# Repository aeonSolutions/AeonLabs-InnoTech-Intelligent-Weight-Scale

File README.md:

[PCB-Prototyping-Catalogue](https://github.com/aeonSolutions/PCB-Prototyping-Catalogue)  >>  [Home-Automation](https://github.com/aeonSolutions/PCB-Prototyping-Catalogue/tree/main/Home-Automation)  >>  [Smart Home Appliances](https://github.com/aeonSolutions/PCB-Prototyping-Catalogue/tree/main/Home-Automation/Smart%20Home%20Appliances)  >>  [Bathroom](https://github.com/aeonSolutions/PCB-Prototyping-Catalogue/tree/main/Home-Automation/Smart%20Home%20Appliances/bathroom) >>  InnoTech Intelligent Weight Scale

<br>

<br />

# AeonLabs InnoTech Intelligent Weight Scale
This smart PCB is a direct replacement of the one that is installed on all InnoTech Weight Scales. Features a color LCD and you can connect to your home automation without the need for third-party cloud storage. **This way your health data never leaves your home**.

A breif view of the original specifications:

- Innotech Smart scale analyze 9 essential measurements of your body, including weight, body fat, water, muscle mass, BMI, BMR, visceral fat, bone mass, and protein. Data easily transferred to the Innotech Scale APP as well as other partners' APPs, it will keep you informed about your body data
- Innotech BMI scale can track the measurement for up to 10 users. Innotech Body Fat Scale helps to track and obtain your family’s daily measurements. This Smart Scale is perfect for family, body builder, weight loser
- 4 built-in sensors that ensure accurate measurement up to 397 lbs/180kg in 0.2 lb/0.1kg increments. Our stylish smart scale boosts an extended surface area with resilient tempered glass for durability. The large LED screen easily displays weight without your mobile device

## PCB

## What one additionally needs
- [USB to UART/USB TTL firmware burner for 5V and 3.3V MCUs ](https://github.com/aeonSolutions/PCB-Prototyping-Catalogue/blob/main/DIY-Maker/README.md) 
<br />
<br />

## Author

You can get in touch with me on my LinkedIn Profile:

#### Miguel Tomas

You can also follow my GitHub Profile to stay updated about my latest projects: 

<br>

### Be supportive of my dedication and work towards technology education and buy me a cup of coffee
The PCB Desgin Files i provide here for anyone to use are free. If you like this Smart Device or use it, please consider buying me a cup of coffee, a slice of pizza or a book to help me study, eat and think new PCB design files.

<br />

### Make a donation on Paypal
Make a donation on paypal and get a TAX refund*.

<br>

### Support all these open hardware projects and become a patreon  
Liked any of my PCB KiCad Designs? Help and Support my open work to all by becomming a LDAD Patreon.
In return I will give a free PCB design in KiCad to all patreon supporters. To learn more go to patreon.com. Link below.

<br />
<br />

______________________________________________________________________________________________________________________________
### License
2023 Creative Commons Attribution-NonCommercial-ShareAlike 4.0 International

https://creativecommons.org/licenses/by-nc-sa/4.0/

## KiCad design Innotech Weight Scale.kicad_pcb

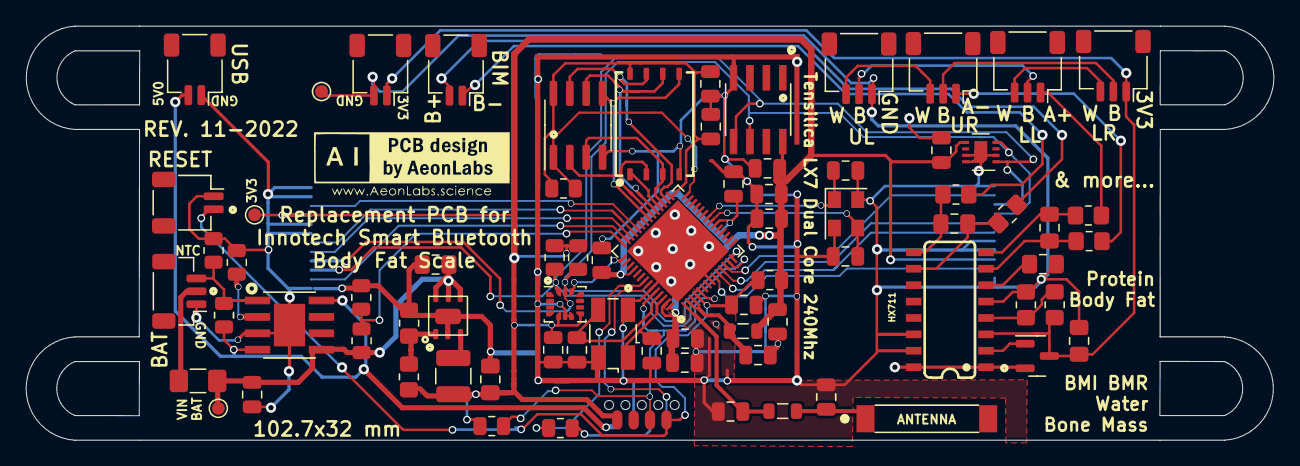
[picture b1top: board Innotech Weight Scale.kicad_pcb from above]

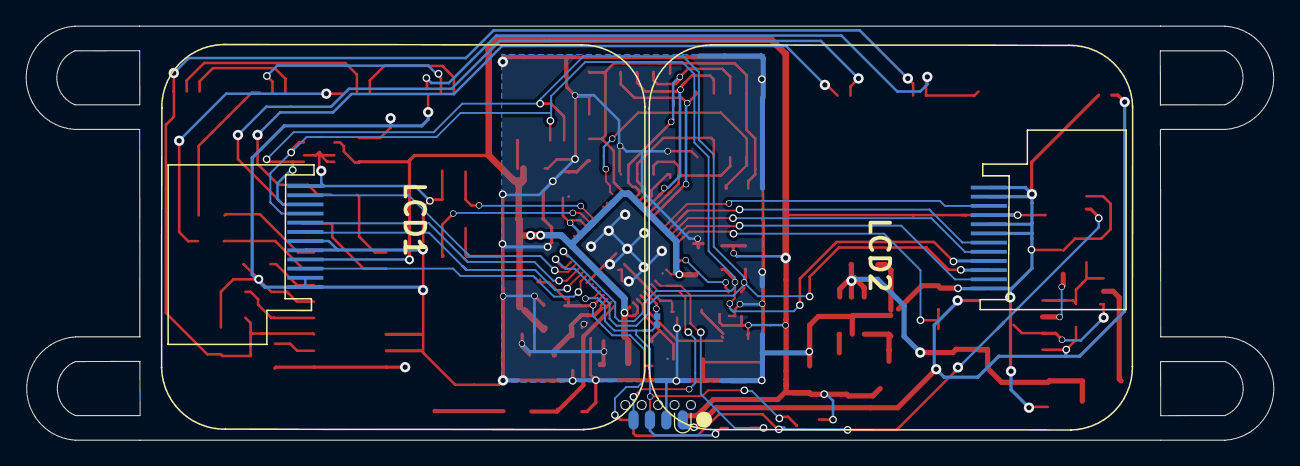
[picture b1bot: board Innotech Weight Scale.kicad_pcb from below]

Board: 2 copper layers, 96.6 x 32.1 mm, 78 parts (3 on the bottom side), 58 nets.

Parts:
2TY1: S8550; SOT-23
AC1: 22uF; C_0805_2012Metric_Pad1.18x1.45mm_HandSolder
AC2: 4.7uF; C_0805_2012Metric_Pad1.18x1.45mm_HandSolder
AL1: 3.3uF; L_1210_3225Metric
ANT1: AN9520; AN9520_ANT2-SMD-9.5X2.1X1.0MM
AR1: 47K; R_0805_2012Metric_Pad1.20x1.40mm_HandSolder
AR2: 15K; R_0805_2012Metric_Pad1.20x1.40mm_HandSolder
AU1: AUR9718x_DFN_3x3mm_6_pin; AUR9718 3x3mm 6 pin
AUC1: 100nF; C_0805_2012Metric
BAT2: BAT1; JST_SH_BM03B-SRSS-TB_1x03-1MP_P1.00mm_Vertical
BMI1: Screw_Terminal_01x02; JST_SH_SM02B-SRSS-TB_1x02-1MP_P1.00mm_Horizontal
BMIPW1: Screw_Terminal_01x02; JST_SH_SM02B-SRSS-TB_1x02-1MP_P1.00mm_Horizontal
EC12, EC13, EC50, EC51: 22pF 5% 50V; C_0805_2012Metric
EC14: 100pF; C_0805_2012Metric
EC15, EC25: 1uF 10% 50V; C_0805_2012Metric
EC16, EC19, EC20, EC24, EC26, EC37, EC38: 100nF 10% 16V; C_0805_2012Metric
EC17, EC18: 10uF 20% 6.3V; C_0805_2012Metric
EC40: 100nF; C_0805_2012Metric
ECY1: 40Mhz 22pF+-10PPM; Crystal_SMD_EuroQuartz_MJ-4Pin_5.0x3.2mm
ECY2: 32.768Mhz 22pF+-10PPM; Crystal_SMD_EuroQuartz_MT-4Pin_3.2x2.5mm
EL4: 12nH 5%; L_0805_2012Metric
EPS1: ESP32-PSRAM_LY68L6400S; SOIC-8_3.9x4.9mm_P1.27mm
ER1, ER3: 10k; R_0805_2012Metric
ER2: 499R; R_0805_2012Metric
ESP32S3: ESP32-S3; QFN-56-1EP_7x7mm_P0.4mm_EP5.6x5.6mm
ESP_FLASH1: W25Q128JVS; W25Q128JV WSON 8x6-mm
F1: Polyfuse; Fuse_1206_3216Metric_Pad1.42x1.75mm_HandSolder
HC1, HC2, HC4: 0.1pF; C_0805_2012Metric_Pad1.18x1.45mm_HandSolder
HC3: 10pF; C_0805_2012Metric_Pad1.18x1.45mm_HandSolder
HR1, HR2, HR5, HR6: 100R; R_0805_2012Metric_Pad1.20x1.40mm_HandSolder
HR3: 8.4k; R_0805_2012Metric_Pad1.20x1.40mm_HandSolder
HR4: 18k4; R_0805_2012Metric_Pad1.20x1.40mm_HandSolder
HX711: HX711; HX711 SO16
ICR1: 10k; R_0805_2012Metric
ICSP1: Conn_01x08_Male; SOIC_clipProgSmall
IDR1: 10k; R_0805_2012Metric
IMU1: LSM6DS3; LGA-14_3x2.5mm_P0.5mm_LayoutBorder3x4y
IMUC1: 100nF; C_0805_2012Metric
L2: 12nH 5%; L_0805_2012Metric
LCD1, LCD2: Conn_01x12_Male; 1,69 inch LCD IPS TFT
LL4: Screw_Terminal_01x03; JST_SH_SM03B-SRSS-TB_1x03-1MP_P1.00mm_Horizontal
LR1: Screw_Terminal_01x03; JST_SH_SM03B-SRSS-TB_1x03-1MP_P1.00mm_Horizontal
MR3: 390K; R_0805_2012Metric
MR4: 110K; R_0805_2012Metric
PSR1: 100K; R_0805_2012Metric
RST1: Conn_01x02_Female; JST_SH_SM02B-SRSS-TB_1x02-1MP_P1.00mm_Horizontal
SH1: SHT31-DIS; Sensirion_DFN-8-1EP_2.5x2.5mm_P0.5mm_EP1.1x1.7mm
SHC1: 100nF; C_0805_2012Metric
TP1: VIN; TestPoint_Pad_D1.0mm
TP2: VOut; TestPoint_Pad_D1.0mm
TP3: GND; TestPoint_Pad_D1.0mm
TPC2: 10uF; C_0805_2012Metric
TPR1, TPR2, TPR3: 1k2; R_0805_2012Metric
TPU1: TP4056; SOP127P600X175-9N TP4056
U2: ATSHA204A-MAHDA-T; ATSHA204A Auth SOIC8
UL2: Screw_Terminal_01x03; JST_SH_SM03B-SRSS-TB_1x03-1MP_P1.00mm_Horizontal
UR3: Screw_Terminal_01x03; JST_SH_SM03B-SRSS-TB_1x03-1MP_P1.00mm_Horizontal
USBCHR1: Screw_Terminal_01x02; JST_SH_SM02B-SRSS-TB_1x02-1MP_P1.00mm_Horizontal

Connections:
3V3: AC1.1, AL1.1, AR1.1, AUC1.2, EC14.2, EC15.2, EC16.1, EC17.1, EC18.1, EC19.1, EC26.1, ER1.1, ER3.1, ESP32S3.20 (VDD3P3_RTC), ESP32S3.46 (VDD3P3_CPU), ESP32S3.55 (VDDA), ESP32S3.56 (VDDA), ICR1.1, ICSP1.8, IDR1.2, IMU1.5 (VDDIO), IMU1.8 (VDD), IMUC1.2, L2.1, LCD1.4, LCD2.4, SH1.5 (VDD), SHC1.2, TP2.1, U2.8 (VCC)
5V0: ICSP1.1, TPR3.2, TPU1.4 (VCC), TPU1.8 (CE), USBCHR1.2
BAT_NTC: BAT2.3, TPR2.2, TPR3.1, TPU1.1 (TEMP)
BAT_SENSE_IO37: ESP32S3.42 (GPIO37), MR3.2, MR4.1
CHIP_EN: EC40.2, ER1.2, ESP32S3.4 (CHIP_PU/RESET), ICSP1.5, RST1.2
ESP_GPIO0_BOOT-DTR: ER3.2, ESP32S3.5 (GPIO0/BOOT), ESP32S3.52 (GPIO46), ICSP1.6
GND: AC1.2, AC2.2, AR2.2, AU1.2 (GND), AUC1.1, BAT2.1, BMIPW1.2, EC12.2, EC13.2, EC14.1, EC15.1, EC16.2, EC17.2, EC18.2, EC19.2, EC20.2, EC24.2, EC25.2, EC26.2, EC37.2, EC38.2, EC40.1, EC50.2, EC51.2, ECY1.2, ECY1.4, ECY2.2, ECY2.4, EPS1.4 (VSS), ESP32S3.8 (GPIO3/ADC1_CH2), ESP32S3.51 (GPIO45), ESP32S3.57 (GND), ESP_FLASH1.4 (GND), HC2.2, HC3.1, HR3.2, HX711.5 (AGND), HX711.14 (XI), HX711.15 (RATE), ICSP1.2, IMU1.6 (GND), IMU1.7 (GND), IMUC1.1, LCD1.1, LCD1.2, LCD1.5, LCD1.6, LCD1.12, LCD2.1, LCD2.2, LCD2.5, LCD2.6, LCD2.12, MR4.2, RST1.1, SH1.2 (ADDR), SH1.7 (R), SH1.8 (VSS), SH1.9 (VSS), SHC1.1, TP3.1, TPC2.2, TPR1.1, TPR2.1, TPU1.3 (GND), TPU1.9 (EP), U2.4 (GND), UL2.1, USBCHR1.1
GPIO8_I2C_SDA: ESP32S3.13 (GPIO8/ADC1_CH7), IDR1.1, IMU1.14 (SDA), LCD1.10, LCD2.10, SH1.1 (SDA), U2.5 (SDA)
GPIO9_I2C_SCL: ESP32S3.14 (GPIO9/ADC1_CH8), ICR1.2, IMU1.13 (SCL), LCD1.9, LCD2.9, SH1.4 (SCL), U2.6 (SCL)
HX_3V3: 2TY1.3 (C), BMIPW1.1, HC3.2, HR4.2, HX711.3 (AVDD), LR1.1
HX_3V3_IO: 2TY1.2 (E), HX711.1 (VSUP), HX711.16 (DVDD)
HX_A+: HR1.2, LL4.1
HX_A-: HR2.2, UR3.1
HX_B+: BMI1.2, HR5.2
HX_B-: BMI1.1, HR6.2
IMU_CS_IO38: ESP32S3.43 (GPIO38), IMU1.12 (CS)
LCD1_CS_IO06: ESP32S3.11 (GPIO6/ADC1_CH5), LCD1.8
LCD1_DC_IO05: ESP32S3.10 (GPIO5/ADC1_CH4), LCD1.7
LCD1_LED_IO04: ESP32S3.9 (GPIO4/ADC1_CH3), LCD1.3
LCD1_RESET_IO07: ESP32S3.12 (GPIO7/ADC1_CH6), LCD1.11
LCD2_CS_IO35: ESP32S3.40 (GPIO35), LCD2.8
LCD2_DC_IO34: ESP32S3.39 (GPIO34), LCD2.7
LCD2_LED_IO33: ESP32S3.38 (GPIO33), LCD2.3
LCD2_RESET_IO36: ESP32S3.41 (GPIO36), LCD2.11
unnamed: 2TY1.1 (B), HX711.2 (BASE)
unnamed: AL1.2, AU1.3 (SW)
unnamed: ANT1.1, EC37.1, EL4.1
unnamed: AR1.2, AR2.1, AU1.1 (FB)
unnamed: EC12.1, ECY1.1, ESP32S3.54 (XTAL_P)
unnamed: EC13.1, ECY1.3, ESP32S3.53 (XTAL_N)
unnamed: EC20.1, ESP32S3.2 (VDD3P3), ESP32S3.3 (VDD3P3), L2.2
unnamed: EC38.1, EL4.2, ESP32S3.1 (LNA_IN/RF)
unnamed: EC50.1, ECY2.1, ESP32S3.22 (GPIO16/ADC2_CH5/XTAL_32K_N)
unnamed: EC51.1, ECY2.3, ESP32S3.21 (GPIO15/ADC2_CH4/XTAL_32K_P)
unnamed: ER2.2, ESP32S3.49 (U0TXD/PROG/GPIO43)
unnamed: HC1.1, HR2.1, HX711.7 (INA-)
unnamed: HC1.2, HR1.1, HX711.8 (INA+)
unnamed: HC2.1, HX711.6 (VBG)
unnamed: HC4.1, HR5.1, HX711.10 (INB+)
unnamed: HC4.2, HR6.1, HX711.9 (INB-)
unnamed: HR3.1, HR4.1, HX711.4 (VFB)
unnamed: LL4.2, UL2.2
unnamed: LL4.3, LR1.3
unnamed: LR1.2, UR3.2
unnamed: TPR1.2, TPU1.2 (PROG)
unnamed: UL2.3, UR3.3
RXD0: ESP32S3.50 (U0RXD/PROG/GPIO44), ICSP1.4
SPICLK: EPS1.6 (SCLK), ESP32S3.33 (SPICLK/GPIO30), ESP_FLASH1.6 (CLK)
SPICS0: ESP32S3.32 (SPICS0/GPIO29), ESP_FLASH1.1 (~CS)
SPICS1: EPS1.1 (~CE), ESP32S3.28 (SPI_CS1/GPIO26), PSR1.1
SPID: EPS1.5 (SiO0), ESP32S3.35 (SPID/GPIO32), ESP_FLASH1.5 (DI(IO0))
SPIHD: EPS1.7 (SIO3), ESP32S3.30 (SPIHD/GPIO27), ESP_FLASH1.7 (IO3)
SPIQ: EPS1.2 (SIO1), ESP32S3.34 (SPIQ/GPIO31), ESP_FLASH1.2 (DO(IO1))
SPIWP: EPS1.3 (SIO2), ESP32S3.31 (SPIWP/GPIO28), ESP_FLASH1.3 (IO2)
TXD0: ER2.1, ICSP1.3
VDD_SPI: EC24.1, EC25.1, EPS1.8 (VCC), ESP32S3.29 (VDD_SPI), ESP_FLASH1.8 (VCC), PSR1.2
VIN_BAT: AC2.1, AU1.4 (VIN_SW), AU1.5 (VIN_A), AU1.6 (EN), F1.1, MR3.1, TP1.1, TPC2.1, TPU1.5 (BAT)
VIN_BATF: BAT2.2, F1.2

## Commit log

2022-10-28 kicad project files
